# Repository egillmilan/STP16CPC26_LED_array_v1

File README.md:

# STP16CPC26 LED array v1
A 8x2 LED array controlled by a STP16CPC26 driver, meant for plugging into a custom board with a µC for controlling the LEDs. Resistor R1 determines the constant current flowing through the LEDs, a 1k resistor results in 20mA flowing through each LED. The LEDs are high efficacy (~180 lm/W) 5630 LEDs from Samsung, part no. SPMWHT541ML5XAWMS5. The dimensions of the board are 21mm x 66.5mm with the pin header.

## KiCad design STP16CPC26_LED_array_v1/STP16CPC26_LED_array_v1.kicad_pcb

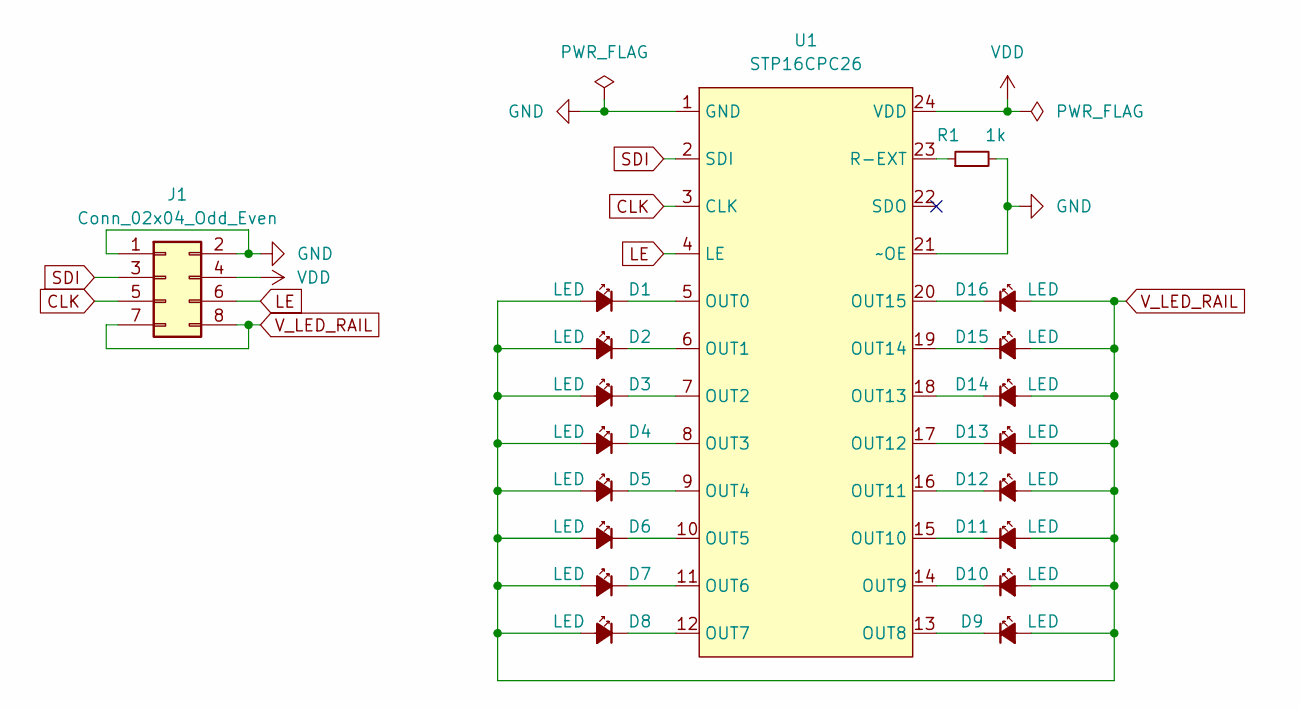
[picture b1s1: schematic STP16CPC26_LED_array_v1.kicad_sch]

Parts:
D1, D2, D3, D4, D5, D6, D7, D8, D9, D10, D11, D12, D13, D14, D15, D16: LED; 5630_LED_Samsung_Hand_Solder; Part# SPMWHT541ML5XAWMS5
J1: Conn_02x04_Odd_Even; PinHeader_2x04_P2.54mm_Horizontal
R1: 1k; R_1206_3216Metric_Pad1.30x1.75mm_HandSolder
U1: STP16CPC26; SOIC-24W_7.5x15.4mm_P1.27mm

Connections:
CLK: J1.5, U1.3 (CLK)
GND: J1.1, J1.2, R1.2, U1.1 (GND), U1.21 (~OE)
LE: J1.6, U1.4 (LE)
unnamed: D1.1 (K), U1.5 (OUT0)
unnamed: D2.1 (K), U1.6 (OUT1)
unnamed: D3.1 (K), U1.7 (OUT2)
unnamed: D4.1 (K), U1.8 (OUT3)
unnamed: D5.1 (K), U1.9 (OUT4)
unnamed: D6.1 (K), U1.10 (OUT5)
unnamed: D7.1 (K), U1.11 (OUT6)
unnamed: D8.1 (K), U1.12 (OUT7)
unnamed: R1.1, U1.23 (R-EXT)
unnamed: D9.1 (K), U1.13 (OUT8)
unnamed: D10.1 (K), U1.14 (OUT9)
unnamed: D11.1 (K), U1.15 (OUT10)
unnamed: D12.1 (K), U1.16 (OUT11)
unnamed: D13.1 (K), U1.17 (OUT12)
unnamed: D14.1 (K), U1.18 (OUT13)
unnamed: D15.1 (K), U1.19 (OUT14)
unnamed: D16.1 (K), U1.20 (OUT15)
SDI: J1.3, U1.2 (SDI)
VDD: J1.4, U1.24 (VDD)
V_LED_RAIL: D1.2 (A), D2.2 (A), D3.2 (A), D4.2 (A), D5.2 (A), D6.2 (A), D7.2 (A), D8.2 (A), D9.2 (A), D10.2 (A), D11.2 (A), D12.2 (A), D13.2 (A), D14.2 (A), D15.2 (A), D16.2 (A), J1.7, J1.8

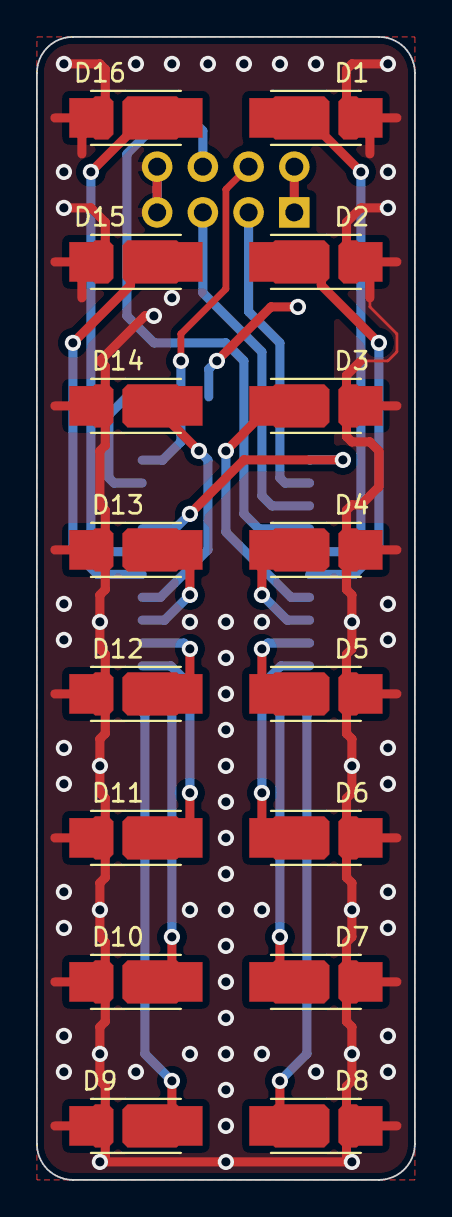
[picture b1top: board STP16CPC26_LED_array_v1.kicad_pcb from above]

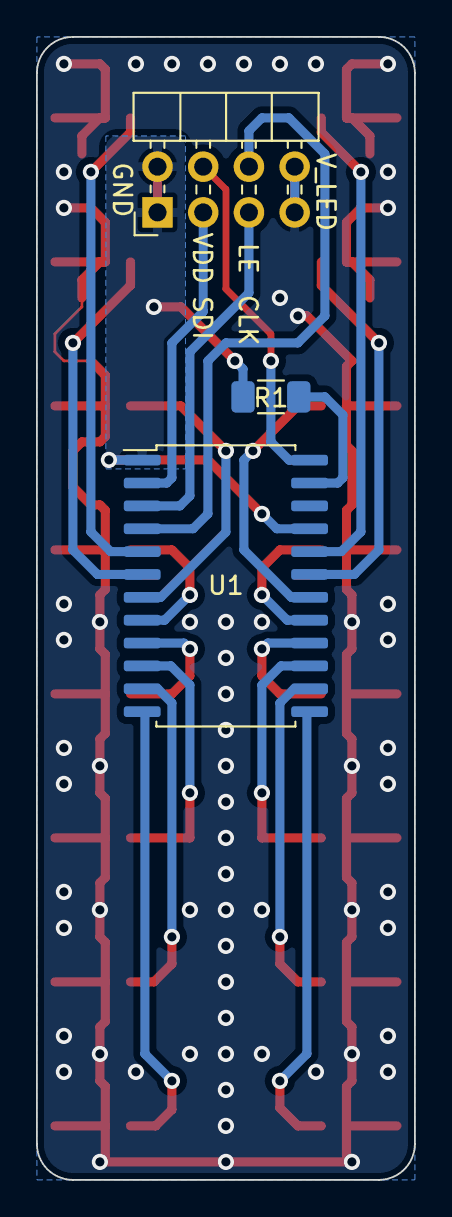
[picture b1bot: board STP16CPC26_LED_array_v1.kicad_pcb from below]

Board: 2 copper layers, 21.0 x 63.5 mm, 19 parts (3 on the bottom side), 23 nets.
